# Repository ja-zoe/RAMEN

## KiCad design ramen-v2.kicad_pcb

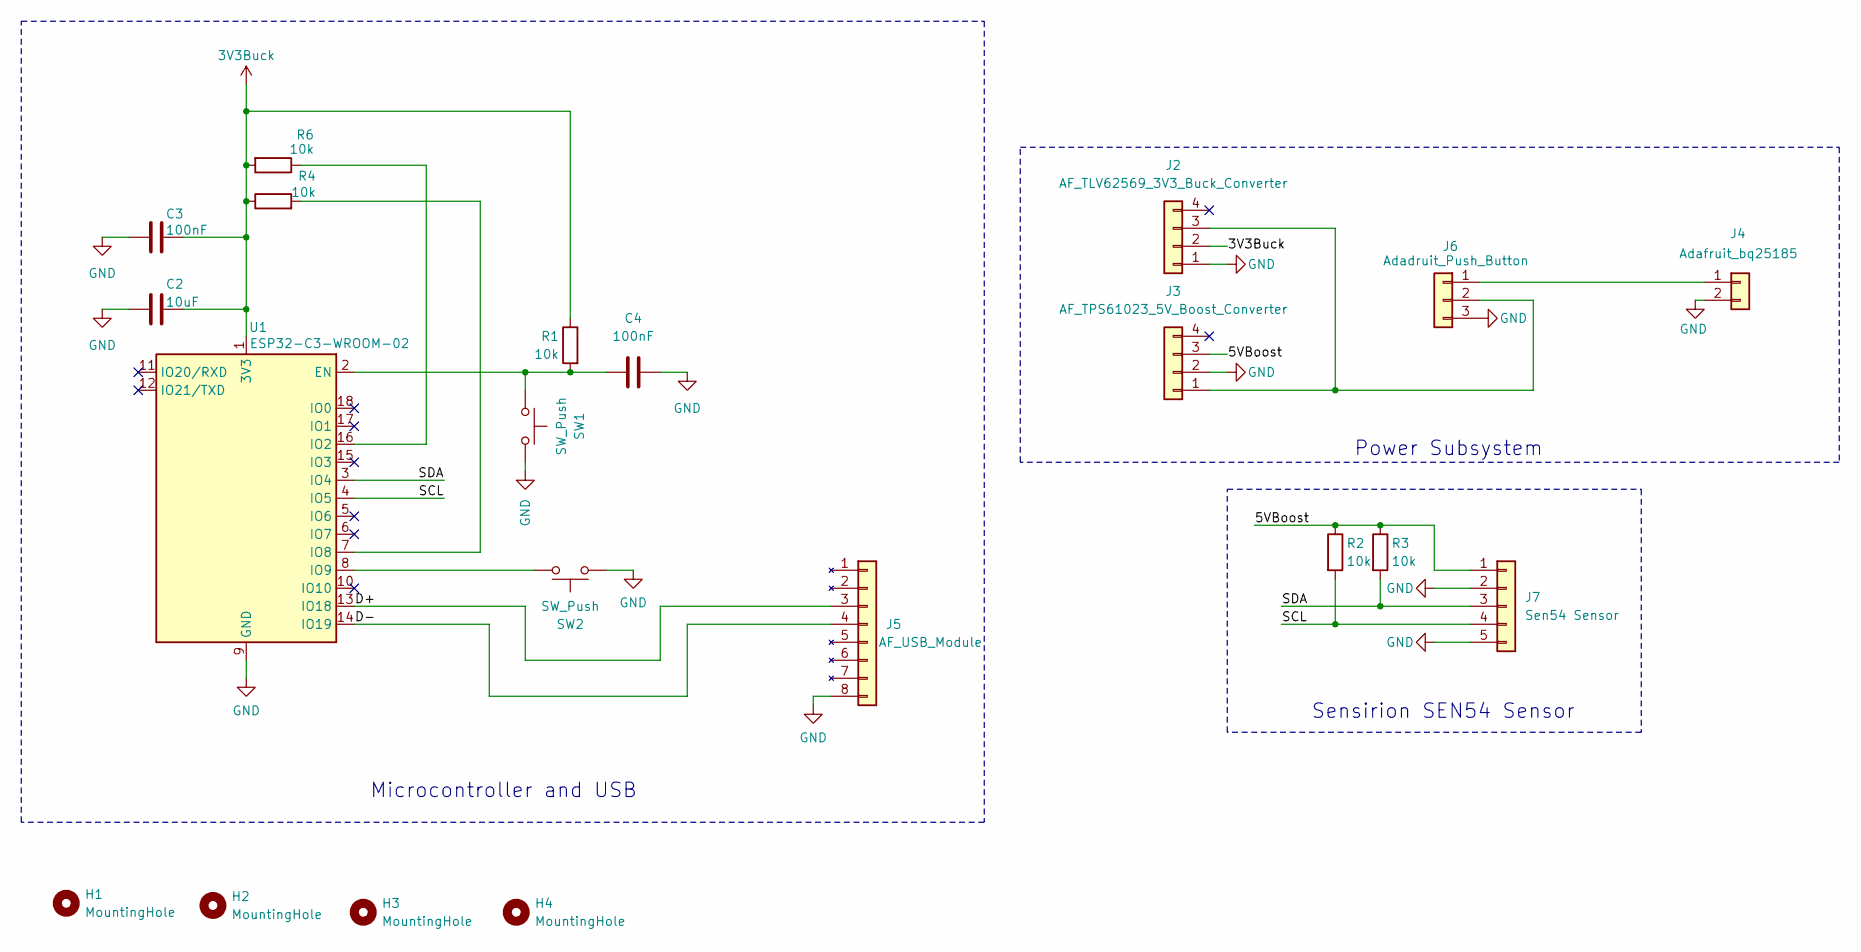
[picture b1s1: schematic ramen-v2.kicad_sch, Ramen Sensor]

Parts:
C2: 10uF; C_1206_3216Metric_Pad1.33x1.80mm_HandSolder
C3, C4: 100nF; C_1206_3216Metric_Pad1.33x1.80mm_HandSolder
H1, H2, H3, H4: MountingHole; MountingHole_2.2mm_M2_DIN965
J2: AF_TLV62569_3V3_Buck_Converter; PinHeader_1x04_P2.54mm_Vertical
J3: AF_TPS61023_5V_Boost_Converter; PinHeader_1x04_P2.54mm_Vertical
J4: Adafruit_bq25185; PinHeader_1x02_P2.54mm_Vertical
J5: AF_USB_Module; PinHeader_1x08_P2.54mm_Vertical
J6: Adadruit_Push_Button; PinHeader_1x03_P2.54mm_Vertical
J7: Sen54 Sensor; PinHeader_1x05_P2.54mm_Vertical
R1, R2, R3, R4, R6: 10k; R_0805_2012Metric_Pad1.20x1.40mm_HandSolder
SW1, SW2: SW_Push; SW_PUSH_6mm
U1: ESP32-C3-WROOM-02

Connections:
3V3Buck: C2.1, C3.1, J2.2 (3V), R1.1, R4.1, R6.2, U1.1 (3V3)
/5VBoost: J3.3 (5V), J7.1 (VDD), R2.1, R3.1
/D+: J5.3 (D+), U1.13 (IO18)
/D-: J5.4 (D-), U1.14 (IO19)
/SCL: J7.4 (SCL), R2.2, U1.4 (IO5)
/SDA: J7.3 (SDA), R3.2, U1.3 (IO4)
GND: C2.2, C3.2, C4.1, J2.1 (GND), J3.2 (GND), J4.2 (load-), J5.8 (GND), J6.3 (GND), J7.2 (GND), J7.5 (SEL), SW1.1, SW2.1, U1.9 (GND), U1.19 (GND)
unnamed: J2.3 (Vin), J3.1 (Vin), J6.2 (Vout)
unnamed: J4.1 (load+), J6.1 (Vin)
unnamed: C4.2, R1.2, SW1.2, U1.2 (EN)
unnamed: R6.1, U1.16 (IO2)
unnamed: R4.2, U1.7 (IO8)
unnamed: SW2.2, U1.8 (IO9)

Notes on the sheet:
Sensirion SEN54 Sensor
Microcontroller and USB
Power Subsystem

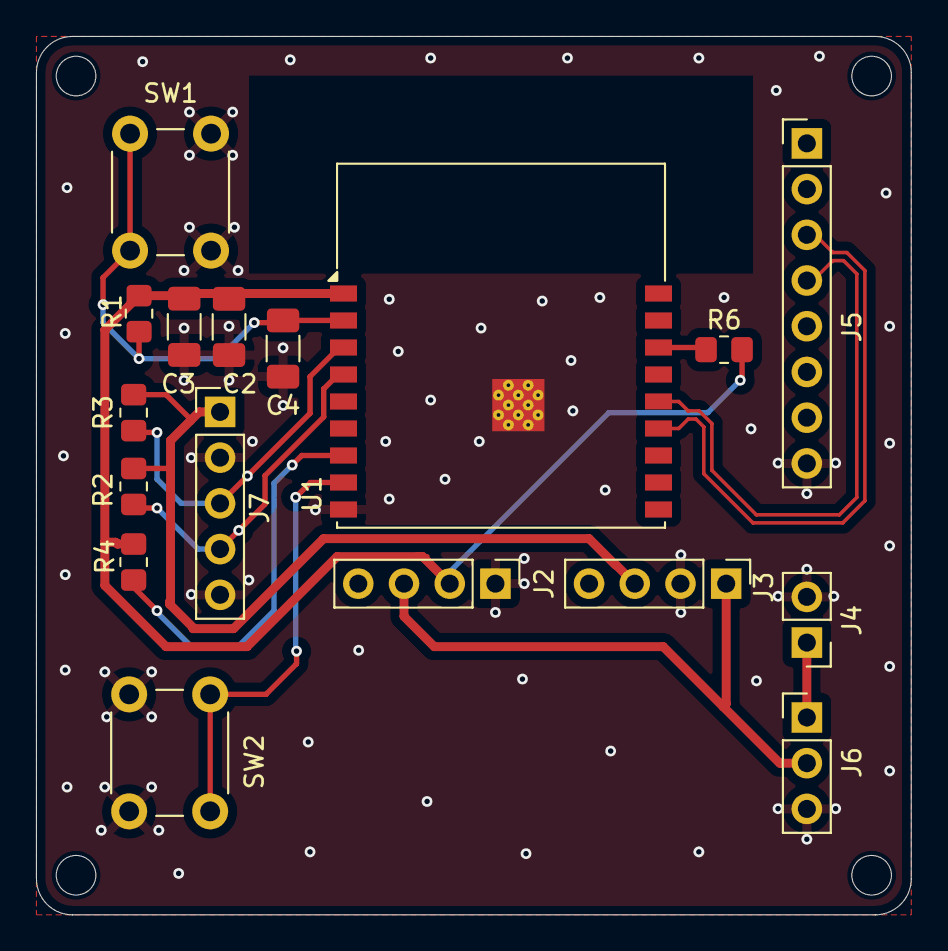
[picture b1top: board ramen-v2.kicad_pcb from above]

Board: 2 copper layers, 48.6 x 48.8 mm, 21 parts (0 on the bottom side), 13 nets.
